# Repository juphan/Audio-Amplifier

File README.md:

# Audio-Amplifier
This audio amplifier circuit was designed to allow the user to physically change the volume of a plugged-in phone (or music player) by turning the dial of a connected dual gauge potentiometer. A phone needs to be connected in series with the potentiometer and the circuit. 

Phone -> Potentiometer -> Circuit (X7)

The circuit will also be connected to a wall outlet and be powered by dampening the incoming AC voltage into DC voltage. A pair of headphones can be connected to the board to project the amplified audio. 

The circuit design was taken from a schematic. This schematic was re-created on Eagle and board layout was performed on a 3x3 inch board. This project mainly involved setting up a circuit, basic board layout, ordering components, and soldering through hole components.

*Note - There is a small design issue. A female pin connector was not included on the circuit for the ground pin of the potentiometer. However, this issue can be solved by manually connecting the ground pin of the potentiometer with another ground in the circuit.

This repository contains the schematic that I re-created in Eagle, the board layout, the generated Gerber files from board layout, and the components list. There is also a picture of the final product.

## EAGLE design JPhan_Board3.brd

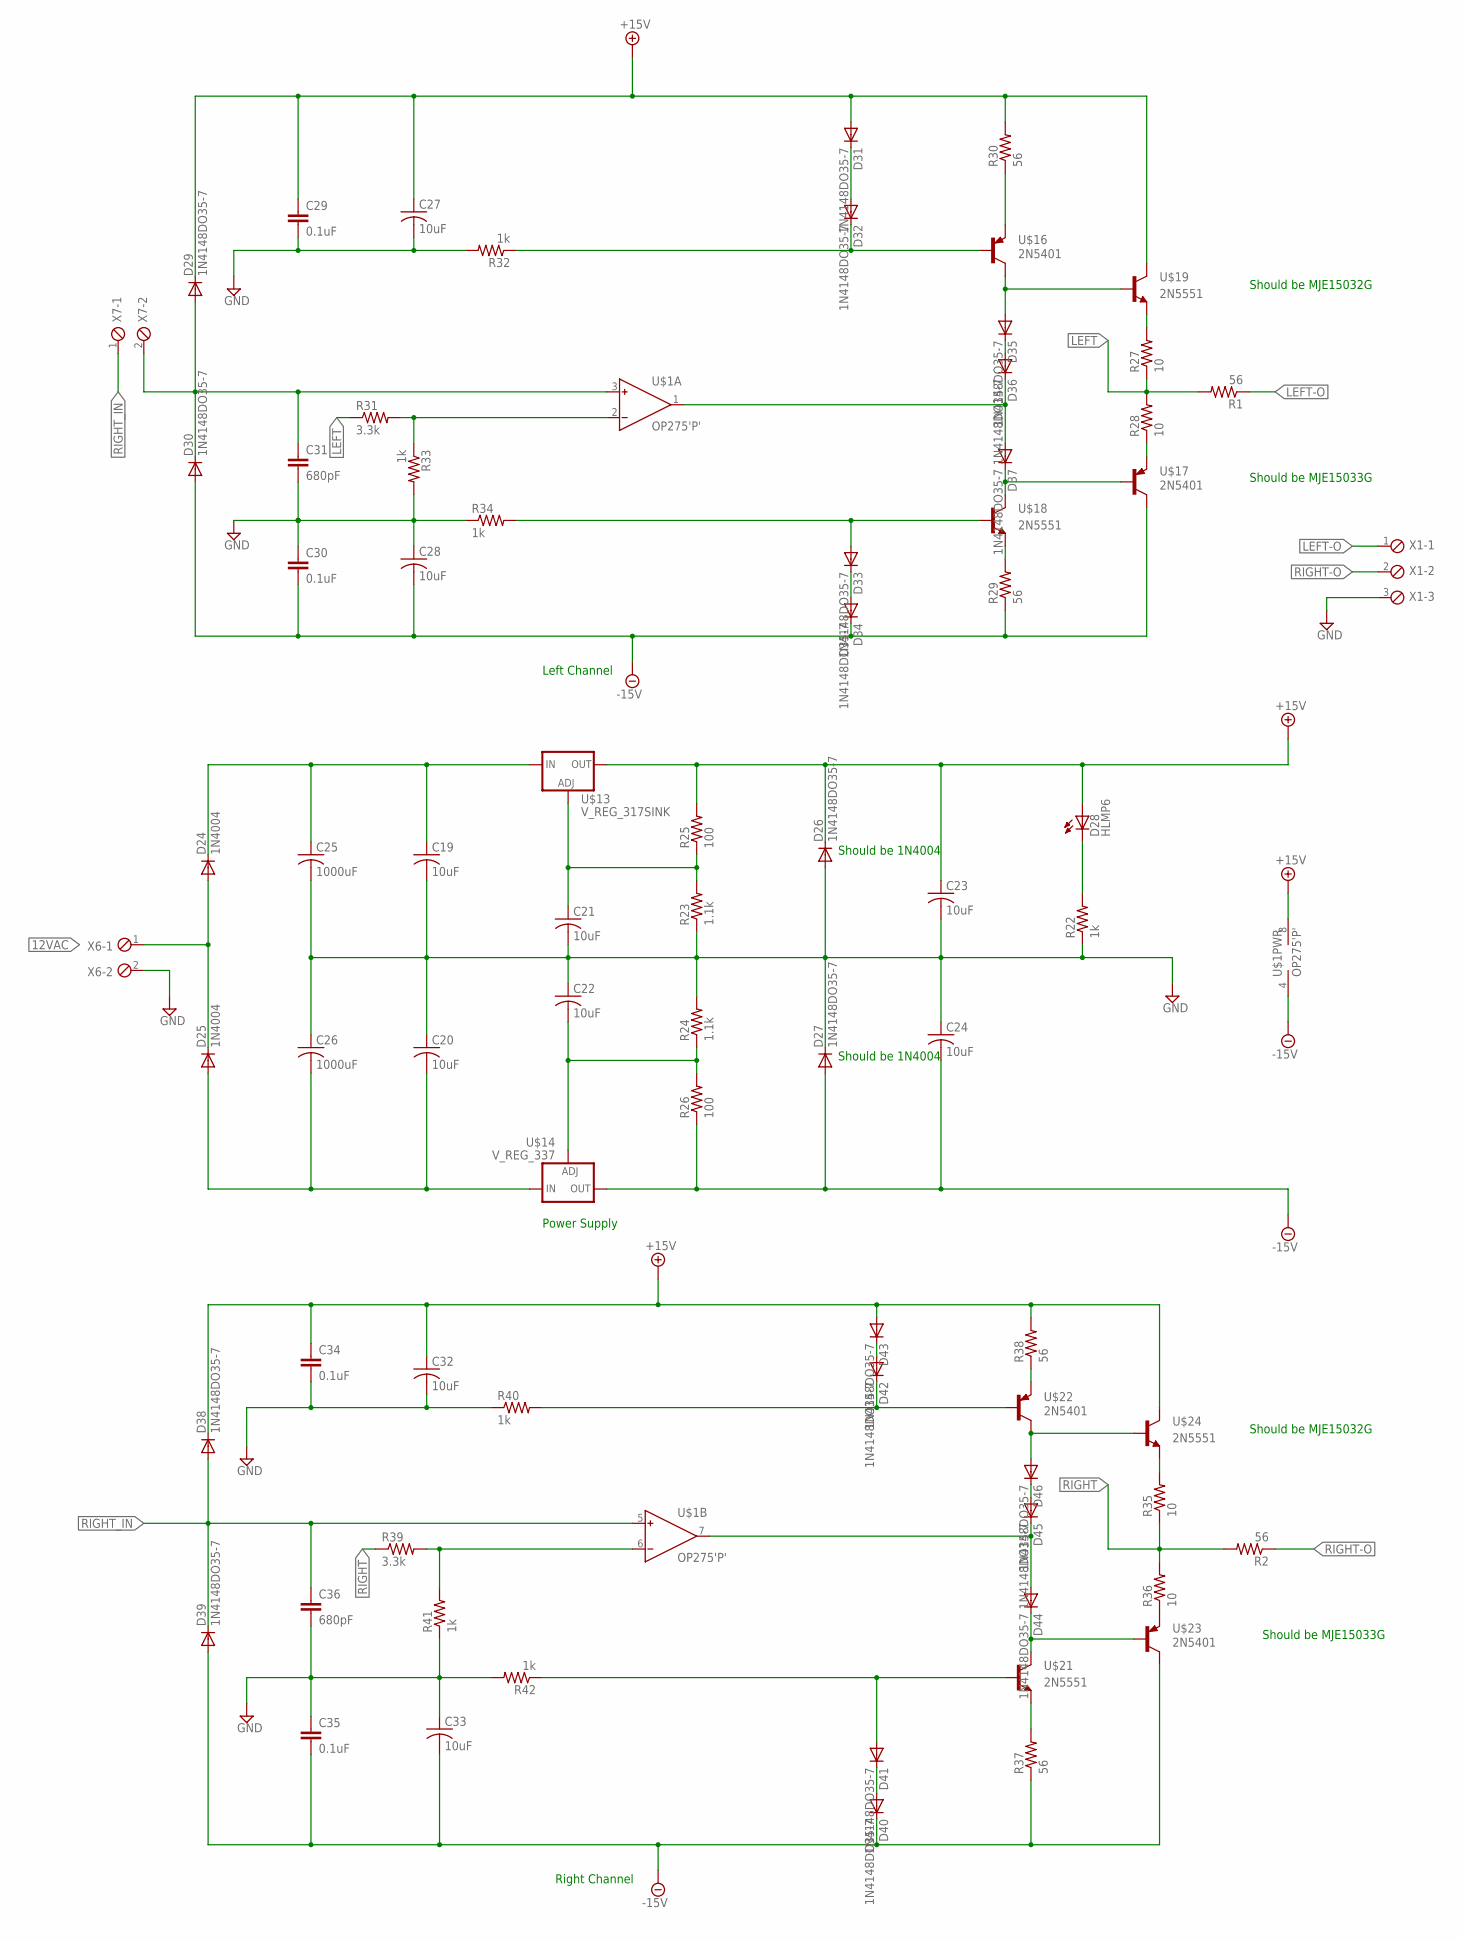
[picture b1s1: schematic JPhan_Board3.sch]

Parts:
C19, C20, C21, C22, C23, C24, C27, C28, C32, C33: 10uF; C025-030X050
C25, C26: 1000uF; C050-045X075
C29, C30, C34, C35: 0.1uF; C025-024X044
C31, C36: 680pF; C025-024X044
D24, D25: 1N4004; DO41-10
D26, D27, D29, D30, D31, D32, D33, D34, D35, D36, D37, D38, D39, D40, D41, D42, D43, D44, D45, D46: 1N4148DO35-7; DO35-7
D28: HLMP6
R1, R2, R29, R30, R37, R38: 56; 0204/7
R22, R32, R33, R34, R40, R41, R42: 1k; 0204/7
R23, R24: 1.1k; 0204/7
R25, R26: 100; 0204/7
R27, R28, R35, R36: 10; 0204/7
R31, R39: 3.3k; 0204/7
U$1: OP275'P'; DIL08
U$13: V_REG_317SINK; TO220-ADJ
U$14: V_REG_337; TO220-ADJ-NEG
U$16, U$17, U$22, U$23: 2N5401
U$18, U$19, U$21, U$24: 2N5551
X1: MPT3; 3POL254
X6, X7: MPT2; 2POL254

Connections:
12VAC: D24.A, D25.C, X6.1
+15V: C23.1, C27.1, C29.1, C32.1, C34.1, D26.C, D28.A, D29.C, D31.A, D38.C, D43.A, R25.2, R30.2, R38.2, U$1.8 (V+), U$13.OUT, U$19.C, U$24.C
-15V: C24.2, C28.2, C30.2, C33.2, C35.2, D27.A, D30.A, D34.C, D39.A, D40.C, R26.1, R29.1, R37.1, U$1.4 (V-), U$14.OUT, U$17.C, U$23.C
GND: C19.2, C20.1, C21.2, C22.1, C23.2, C24.1, C25.2, C26.1, C27.2, C28.1, C29.2, C30.1, C31.2, C32.2, C33.1, C34.2, C35.1, C36.2, D26.A, D27.C, R22.1, R23.1, R24.2, R32.2, R33.2, R34.1, R40.1, R41.1, R42.2, X1.3, X6.2
LEFT: R1.2, R27.1, R28.2, R31.1
LEFT-O: R1.1, X1.1
unnamed: C31.1, D29.A, D30.C, U$1.3 (IN+), X7.2
unnamed: R31.2, R33.1, U$1.2 (IN-)
unnamed: C19.1, C25.1, D24.C, U$13.IN
unnamed: C20.2, C26.2, D25.A, U$14.IN
unnamed: C21.1, R23.2, R25.1, U$13.ADJ
unnamed: C22.2, R24.1, R26.2, U$14.ADJ
unnamed: D28.K, R22.2
unnamed: D35.A, U$16.C, U$19.B
unnamed: D32.C, R32.1, U$16.B
unnamed: D31.C, D32.A
unnamed: R30.1, U$16.E
unnamed: D35.C, D36.A
unnamed: D36.C, D37.A, U$1.1 (OUT)
unnamed: D37.C, U$17.B, U$18.C
unnamed: R29.2, U$18.E
unnamed: D33.C, D34.A
unnamed: R27.2, U$19.E
unnamed: R28.1, U$17.E
unnamed: D33.A, R34.2, U$18.B
unnamed: R39.2, R41.2, U$1.6 (IN-)
unnamed: D40.A, D41.C
unnamed: R37.2, U$21.E
unnamed: D44.C, U$21.C, U$23.B
unnamed: D44.A, D45.C, U$1.7 (OUT)
unnamed: D45.A, D46.C
unnamed: D46.A, U$22.C, U$24.B
unnamed: D42.A, D43.C
unnamed: D42.C, R40.2, U$22.B
unnamed: D41.A, R42.1, U$21.B
unnamed: R35.2, U$24.E
unnamed: R36.1, U$23.E
unnamed: R38.1, U$22.E
RIGHT: R2.2, R35.1, R36.2, R39.1
RIGHT-O: R2.1, X1.2
RIGHT_IN: C36.1, D38.A, D39.C, U$1.5 (IN+), X7.1

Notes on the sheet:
Power Supply
Left Channel
Right Channel
Should be MJE15032G
Should be MJE15033G
Should be 1N4004

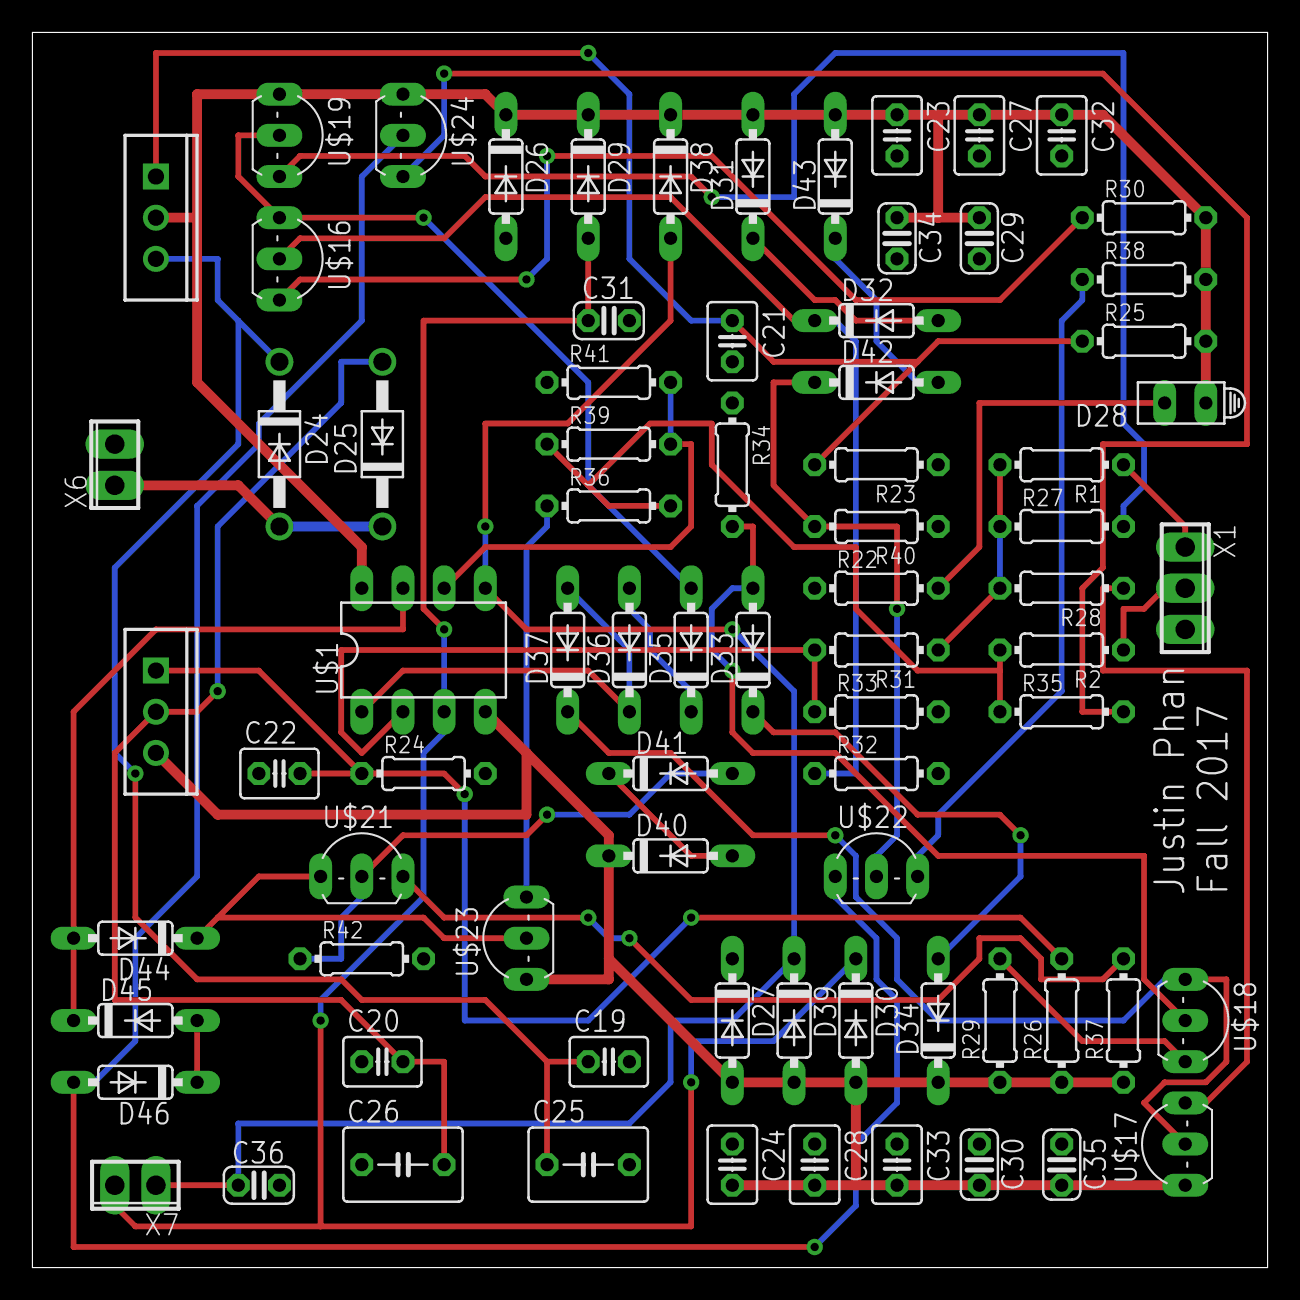
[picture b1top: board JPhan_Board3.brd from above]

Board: 2 copper layers, 76.2 x 76.2 mm, 78 parts (0 on the bottom side), 41 nets.

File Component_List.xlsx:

*Note - Quantity of parts are meant for 3 sets of the Audio Amplifier circuit
Index | Piece | Quantity | Description | Part Number | Description | Unit Price ($) | Extended Price ($)
1 | Capacitors | 30 | 10uF | 445-8290-ND | CAP CER 10UF 16V X5R RADIAL | 0.31900000000000001 | 9.57
2 |  | 6 | 1000uF | 1189-1583-1-ND | CAP ALUM 1000UF 20% 25V RADIAL | 0.67 | 4.0199999999999996
3 |  | 12 | 0.1uF | 505-MKS2.1/63/5 | Film Capacitors 63V .1uF 5% | 0.28899999999999998 | 3.47
4 |  | 6 | 680pF | 505-FKP2680/100/5, wima | Film Capacitors 100V 680pF 5% TOL PCM 5 | 0.76 | 4.5599999999999996
5 | Resistors | 10 | 100 ohm | S100QCT-ND | RES 100 OHM 1/4W 5% CF MINI | 4.1000000000000002E-2 | 0.41
6 |  | 10 | 1.1 kohm | S1.1KQCT-ND | RES 1.1K OHM 1/4W 5% CF MINI | 4.1000000000000002E-2 | 0.41
7 |  | 25 | 1 kohm | S1KQCT-ND | RES 1K OHM 1/4W 5% CF MINI | 0.03 | 0.75
8 |  | 10 | 3.3 kohm | S3.3KQCT-ND | RES 3.3K OHM 1/4W 5% CF MINI | 4.1000000000000002E-2 | 0.41
9 |  | 12 | 56 ohm | BC3946CT-ND | RES 56 OHM 0.4W 5% AXIAL | 0.19700000000000001 | 2.36
10 |  | 6 | 56 ohm/ 1W | P56W-1BK-ND | RES 56 OHM 1W 5% AXIAL | 0.24 | 1.44
11 |  | 12 | 10 ohm | BC3924CT-ND | RES 10 OHM 0.4W 1% AXIAL | 0.19700000000000001 | 2.36
12 | Diodes | 100 | 1N4148 DIODE | 1N4148FS-ND | DIODE GEN PURP 100V 200MA DO35 | 3.4500000000000003E-2 | 3.45
13 |  | 12 | 1N4004 DIODE | 1N4004-TPMSCT-ND | DIODE GEN PURP 400V 1A DO41 | 0.104 | 1.25
14 | Voltage Regs | 3 | V_REG POS | LM338T/NOPB-ND | IC REG LINEAR POS ADJ 5A TO220-3 | 2.1 | 6.3
15 |  | 3 | V_REG NEG | LM337TFS-ND | IC REG LIN NEG ADJ 1.5A TO220-3 | 0.73 | 2.19
16 | LED | 3 | BLUE LED | 1125-1190-ND | LED BLUE DIFF 5MM OVAL T/H | 0.51 | 1.53
17 | Connectors | 6 | 2 PORT CONNECTOR | S7000-ND | CONN HEADER FEMALE 2POS .1" TIN | 0.32 | 1.92
18 |  | 1 | 3 PORT CONNECTOR | S7036-ND | CONN HEADER FEMALE 3POS .1" GOLD | 0.37 | 0.37
19 | OP Amp | 3 | OP AMP | OP275GPZ-ND | IC OPAMP AUDIO 9MHZ 8DIP | 3.43 | 10.29
20 | Transistors | 6 | NPN TRANSISTOR | MJE15032GOS-ND | TRANS NPN 250V 8A TO220AB | 1.58 | 9.48
21 |  | 6 | PNP TRANSISTOR | MJE15033GOS-ND | TRANS PNP 250V 8A TO220AB | 1.58 | 9.48
22 |  | 6 | NPN TRANSISTOR | 2N5551TAFSCT-ND | TRANS NPN 160V 0.6A TO-92 | 0.24 | 1.44
23 |  | 6 | PNP TRANSISTOR | 2N5401CS-ND | TRANS PNP 150V 0.6A TO-92 | 0.49 | 2.94
24 | Audio Jack | 3 | 3.5mm stereo jack | SJ1-3533NG | CONN JACK STEREO 3.5MM R/A | 1.17 | 3.51
 |  |  |  |  |  | Subtotal | 83.91
